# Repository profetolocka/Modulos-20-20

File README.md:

# Módulos 20x20

Este repositorio contiene una colección de módulos electrónicos de 20x20 mm diseñados especialmente para su uso educativo junto a la placa PyTrainer y la plataforma NanoBot.

## 🧩 ¿Qué son los Módulos 20x20?

Los Módulos 20x20 son pequeñas placas electrónicas que siguen un formato cuadrado de 20 mm de lado. Están pensadas para ser:

- Fáciles de montar gracias a su tamaño estandarizado.
- Compatibles con estructuras impresas en 3D con perforaciones espaciadas cada 20 mm.
- Fabricables con técnicas caseras (PCB de una o doble cara, sin componentes SMD).

Estos módulos permiten trabajar conceptos básicos de electrónica y programación de forma práctica, modular y didáctica.

## 🛠️ Módulos disponibles

Cada módulo cuenta con su propia carpeta que incluye:

- Archivos de diseño (Esquemático, PCB).
- Información técnica y de montaje.
- Instrucciones de uso.

Listado actual de módulos incluidos:

- ✅ Módulo LED de 10 mm
- ✅ Módulo con 3 LEDs
- ✅ Módulo con LDR
- ✅ Módulo con LED RGB Neopixel
- ✅ Módulo semáforo (Rojo, Amarillo, Verde)
- ✅ Módulo seguidor de línea
- ✅ Módulo con interruptor

## 🎓 ¿A quién está dirigido?

Este proyecto está pensado para:

- Docentes que deseen implementar actividades prácticas en el aula.
- Estudiantes de nivel medio o inicial en electrónica.
- Makers y entusiastas que busquen una base modular para prototipado.

## 📄 Licencia

Este repositorio se distribuye bajo la licencia [MIT](LICENSE), lo que permite su uso, modificación y redistribución con fines educativos o personales.

---

### ✉️ Contacto

Para sugerencias, mejoras o consultas, podés visitar mi blog: [https://www.profetolocka.com.ar](https://www.profetolocka.com.ar)

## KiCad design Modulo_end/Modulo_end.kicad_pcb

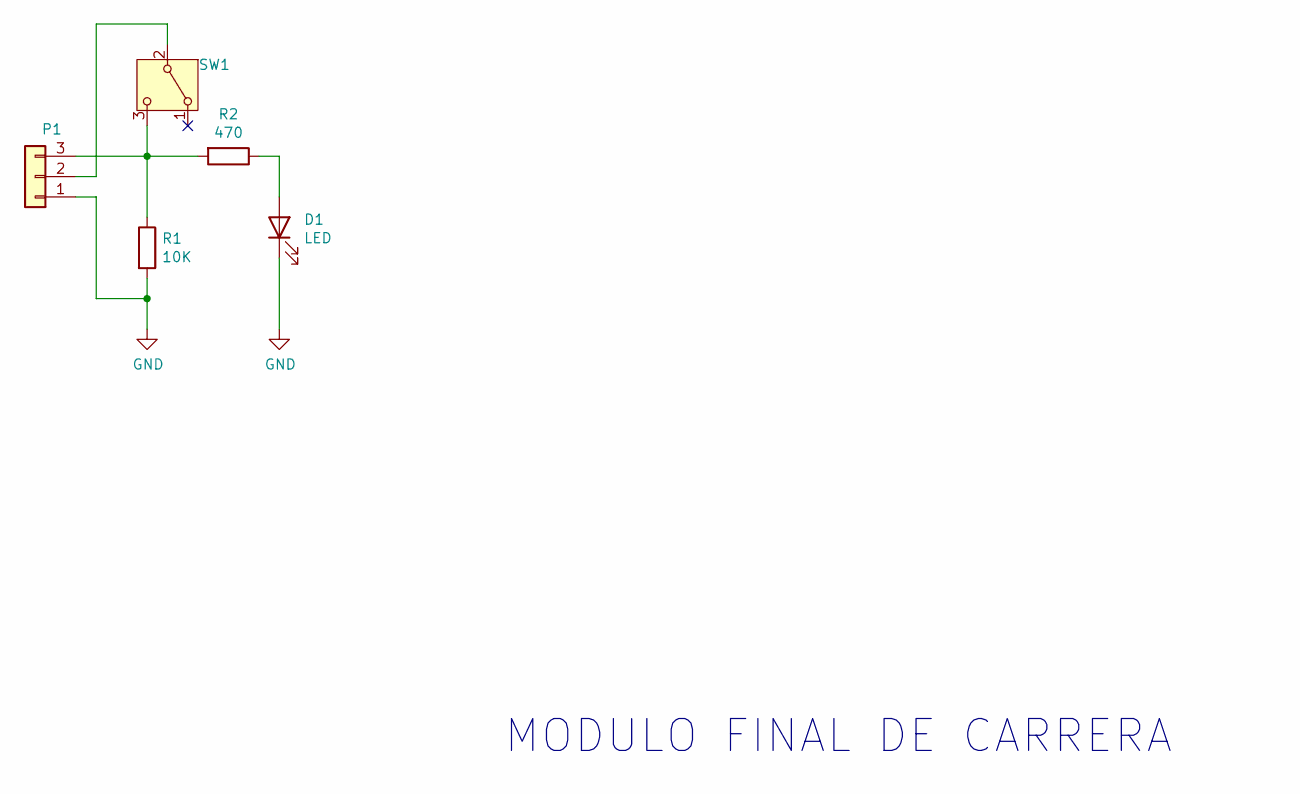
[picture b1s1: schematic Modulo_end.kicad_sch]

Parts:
D1: LED; LED_D3.0mm
P1: Conn_01x03; PinSocket_1x03_P2.54mm_Horizontal
R1: 10K; R_Axial_DIN0204_L3.6mm_D1.6mm_P5.08mm_Horizontal
R2: 470; R_Axial_DIN0204_L3.6mm_D1.6mm_P5.08mm_Horizontal
SW1: SW_SPDT; SW_Toggle_Blue_wSlots

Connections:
GND: D1.1 (K), P1.1, R1.2
unnamed: D1.2 (A), R2.1
unnamed: P1.2, SW1.2 (B)
unnamed: P1.3, R1.1, R2.2, SW1.3 (C)

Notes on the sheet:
MODULO FINAL DE CARRERA

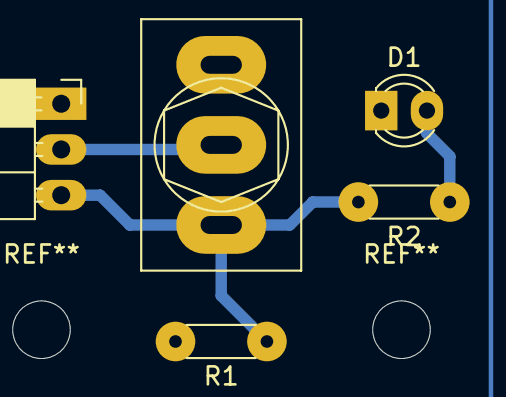
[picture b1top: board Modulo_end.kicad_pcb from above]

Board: 2 copper layers, 5 parts (0 on the bottom side), 4 nets.

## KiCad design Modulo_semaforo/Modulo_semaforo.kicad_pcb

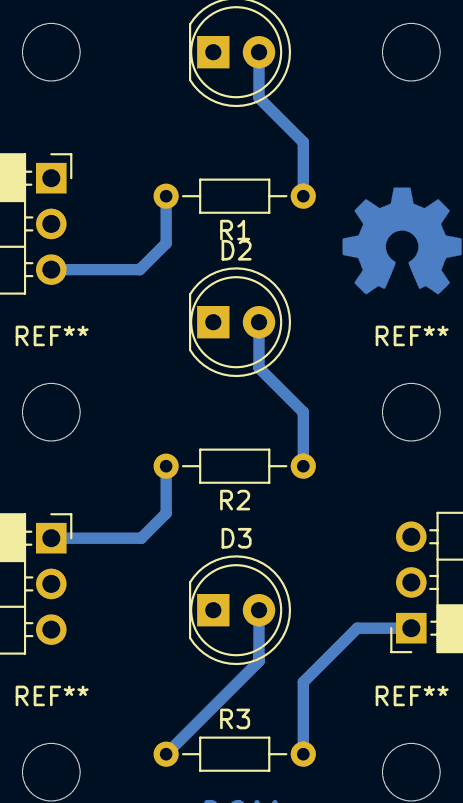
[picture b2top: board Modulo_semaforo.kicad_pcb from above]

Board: 2 copper layers, 9 parts (0 on the bottom side), 7 nets.

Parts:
D1: ROJO; LED_D5.0mm
D2: AMARILLO; LED_D5.0mm
D3: VERDE; LED_D5.0mm
J1, J2, J3: Conn_01x03; PinSocket_1x03_P2.54mm_Horizontal
R1, R2, R3: 470; R_Axial_DIN0204_L3.6mm_D1.6mm_P7.62mm_Horizontal

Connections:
GND: D1.1, D2.1, D3.1, J1.1, J2.3, J3.3
unnamed: D1.2, R1.1
unnamed: D2.2, R2.1
unnamed: D3.2, R3.1
unnamed: J1.3, R1.2
unnamed: J2.1, R2.2
unnamed: J3.1, R3.2

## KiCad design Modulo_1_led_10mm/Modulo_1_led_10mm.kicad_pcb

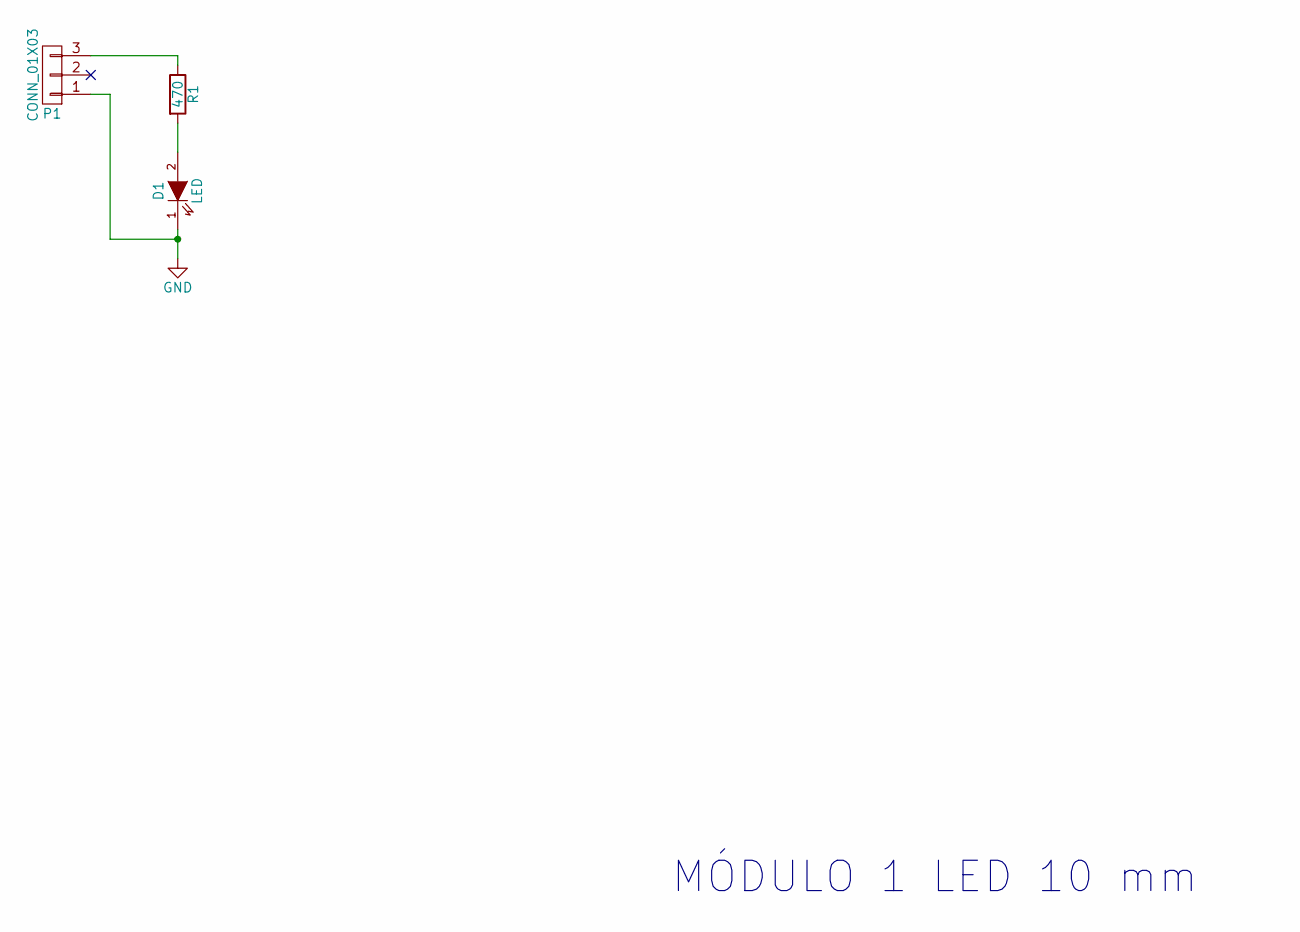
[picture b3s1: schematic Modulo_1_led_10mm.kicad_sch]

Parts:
D1: LED; LED_D10.0mm
P1: CONN_01X03; Socket_Strip_Angled_1x03_Pitch2.54mm
R1: 470; R_Axial_DIN0204_L3.6mm_D1.6mm_P7.62mm_Horizontal

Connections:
GND: D1.1 (K), P1.1
unnamed: D1.2 (A), R1.2
unnamed: P1.3, R1.1

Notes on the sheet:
MÓDULO 1 LED 10 mm

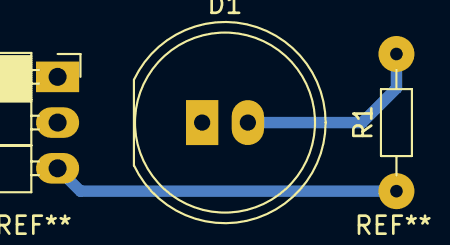
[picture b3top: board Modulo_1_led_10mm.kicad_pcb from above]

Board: 2 copper layers, 3 parts (0 on the bottom side), 3 nets.

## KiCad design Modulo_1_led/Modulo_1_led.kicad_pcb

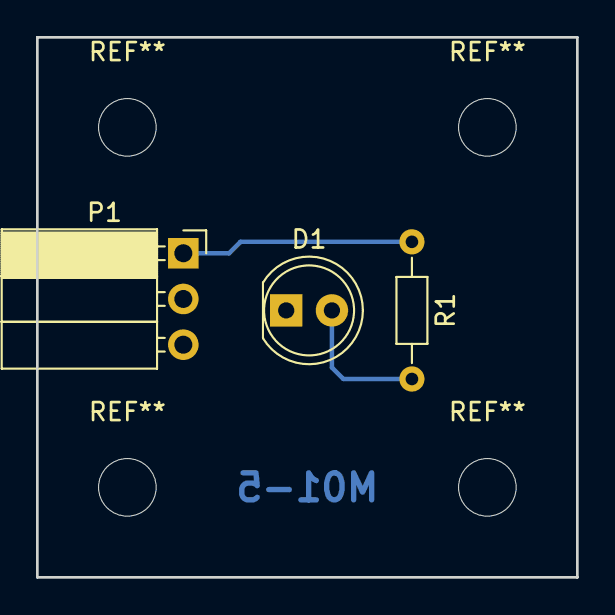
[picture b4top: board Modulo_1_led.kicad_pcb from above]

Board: 2 copper layers, 30.0 x 30.0 mm, 3 parts (0 on the bottom side), 3 nets.

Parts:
D1: LED; LED_D5.0mm
P1: CONN_01X03; Socket_Strip_Angled_1x03_Pitch2.54mm
R1: 470; R_Axial_DIN0204_L3.6mm_D1.6mm_P7.62mm_Horizontal

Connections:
GND: D1.1, P1.3
unnamed: D1.2, R1.2
unnamed: P1.1, R1.1

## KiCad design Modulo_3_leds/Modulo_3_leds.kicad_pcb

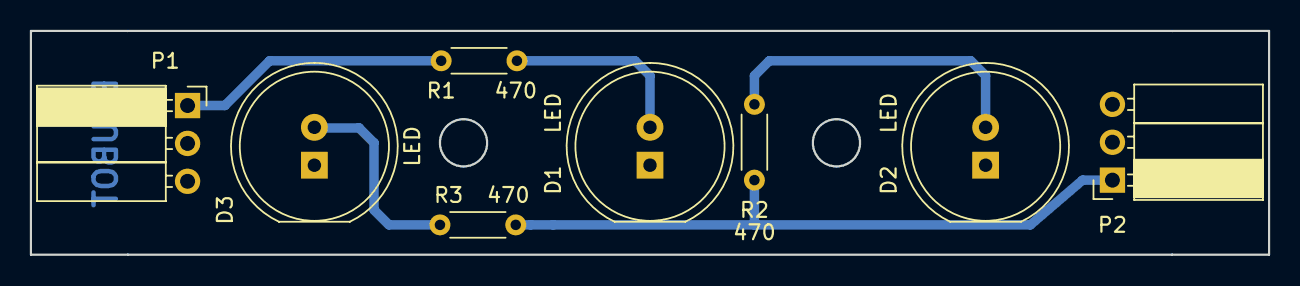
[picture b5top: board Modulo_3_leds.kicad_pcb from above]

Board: 2 copper layers, 83.0 x 15.0 mm, 8 parts (0 on the bottom side), 6 nets.

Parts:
D1, D2, D3: LED; LED_D10.0mm
P1, P2: CONN_01X03; Socket_Strip_Angled_1x03_Pitch2.54mm
R1, R2, R3: 470; R_Axial_DIN0204_L3.6mm_D1.6mm_P5.08mm_Horizontal

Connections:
GND: D1.1, D2.1, D3.1, P1.3, P2.3
unnamed: D1.2, R1.2
unnamed: D2.2, R2.2
unnamed: D3.2, R3.2
unnamed: P1.1, R1.1
unnamed: P2.1, R2.1, R3.1

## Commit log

2025-05-03 Proyecto creado
